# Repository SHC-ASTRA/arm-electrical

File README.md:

# Arm Electrical

Includes the KiCAD files for the Socket and Digit PCBs; Socket is located at the base of Arm and controls the Arm's main joints, Digit is located at the end of Arm and controls Wrist and End Effector.

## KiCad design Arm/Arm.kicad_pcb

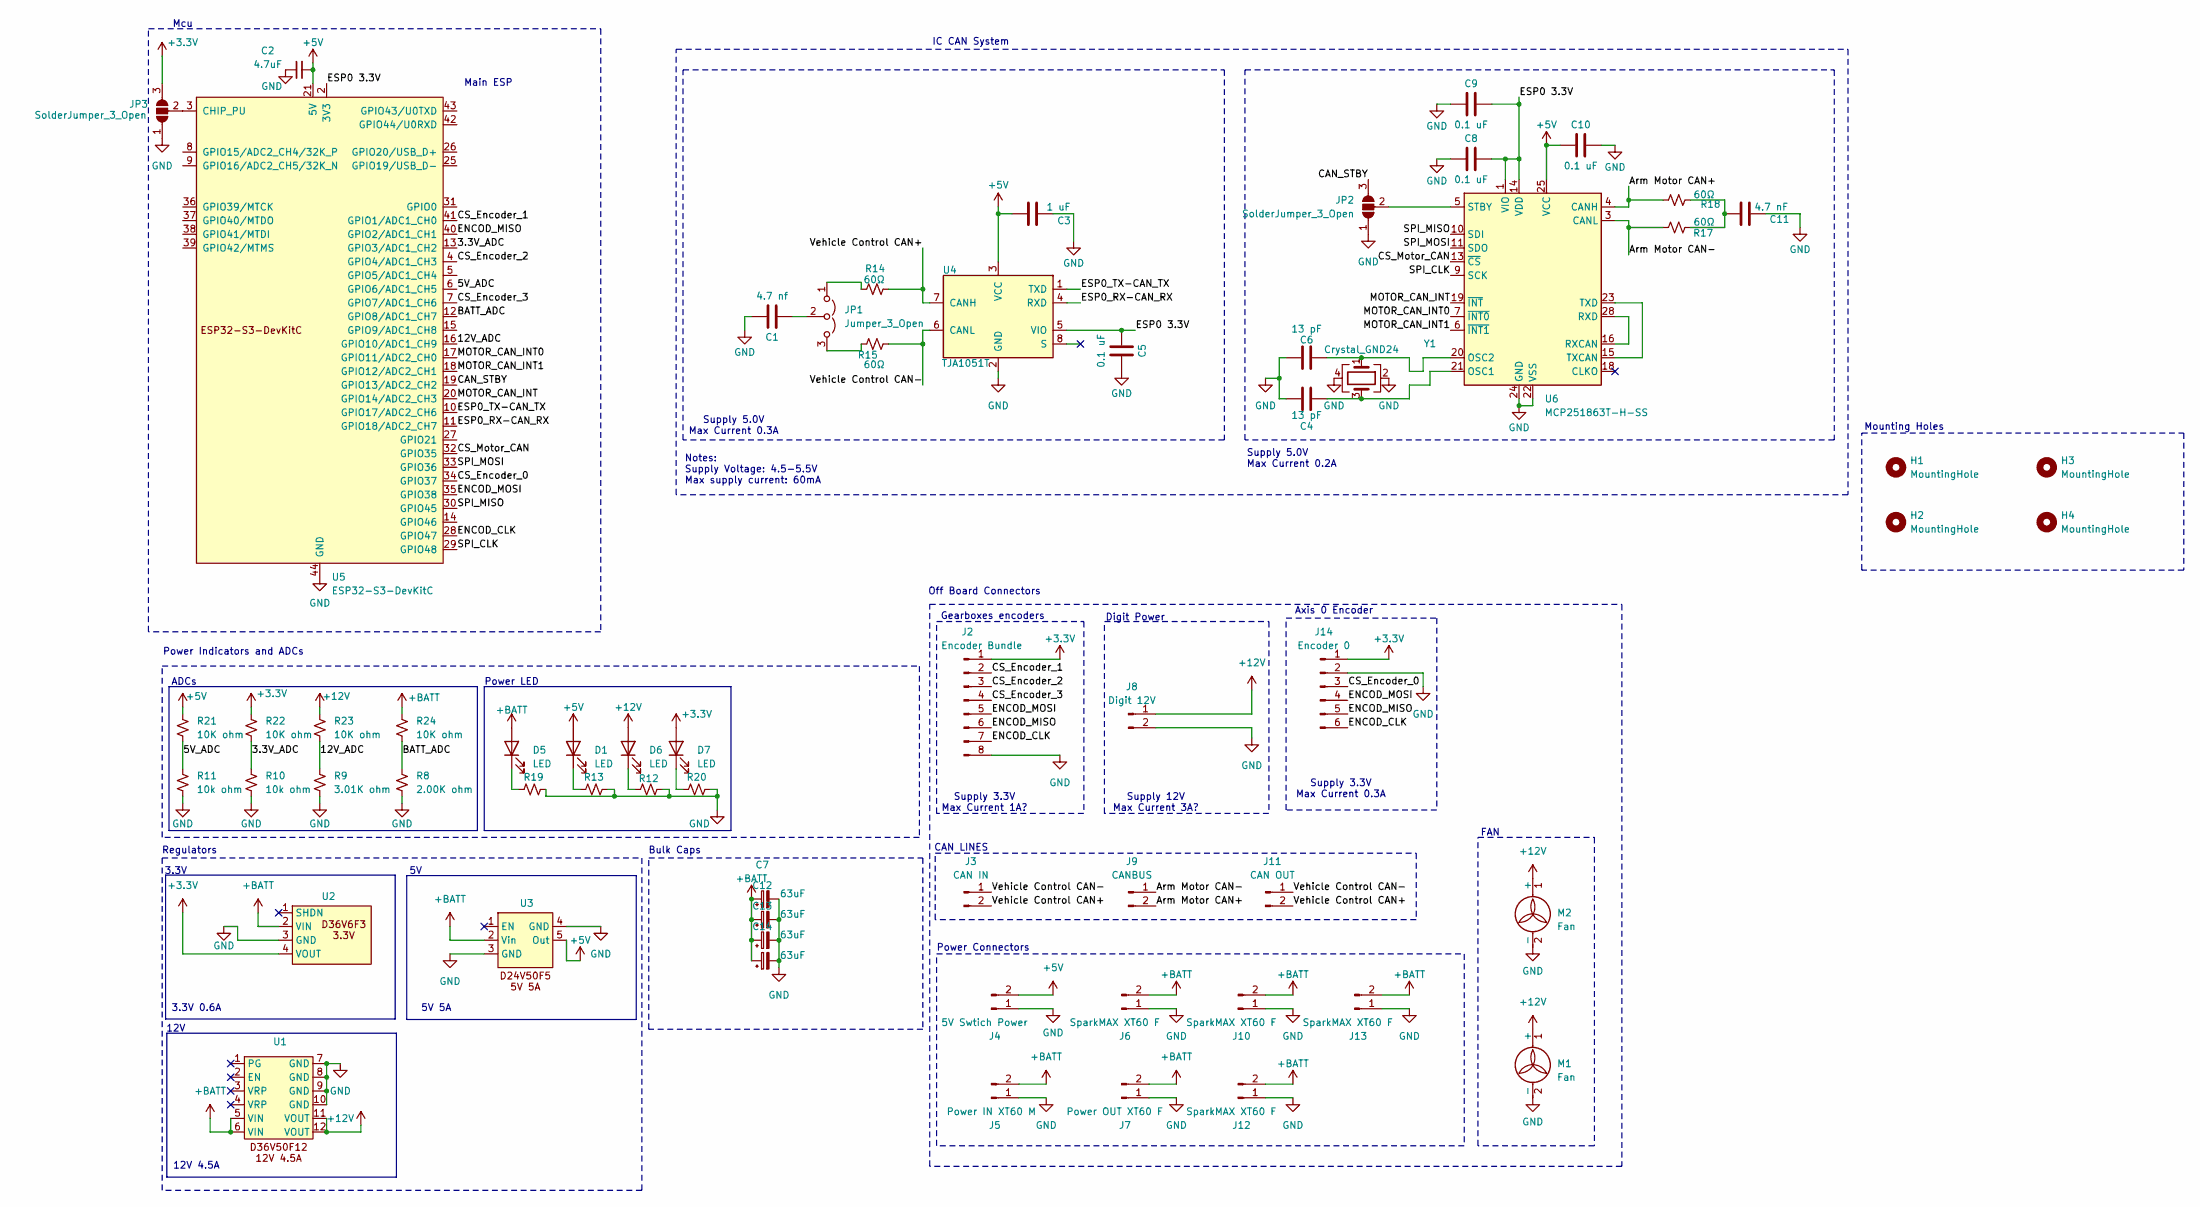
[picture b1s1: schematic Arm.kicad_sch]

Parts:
C1: 4.7 nf; C_0603_1608Metric_Pad1.08x0.95mm_HandSolder
C2: 4.7uF; C_0603_1608Metric_Pad1.08x0.95mm_HandSolder
C3: 1 uF; C_0603_1608Metric_Pad1.08x0.95mm_HandSolder
C4, C6: 13 pF; C_0603_1608Metric_Pad1.08x0.95mm_HandSolder
C5, C8, C9, C10: 0.1 uF; C_0603_1608Metric_Pad1.08x0.95mm_HandSolder
C7, C12, C13, C14: 63uF; CP_Elec_6.3x7.7
C11: 4.7 nF; C_0603_1608Metric_Pad1.08x0.95mm_HandSolder
D1, D5, D6, D7: LED; LED_0603_1608Metric_Pad1.05x0.95mm_HandSolder
H1, H2, H3, H4: MountingHole; MountingHole_3.2mm_M3_DIN965_Pad_TopBottom
J2: Encoder Bundle; Molex_Mini-Fit_Jr_5566-08A_2x04_P4.20mm_Vertical
J3: CAN IN; AMASS_XT30U-F_1x02_P5.0mm_Vertical
J4: 5V Swtich Power; Molex_Mini-Fit_Jr_5566-02A_2x01_P4.20mm_Vertical
J5: Power IN XT60 M; AMASS_XT60-M_1x02_P7.20mm_Vertical
J6, J10, J12, J13: SparkMAX XT60 F; AMASS_XT60-F_1x02_P7.20mm_Vertical
J7: Power OUT XT60 F; AMASS_XT60-F_1x02_P7.20mm_Vertical
J8: Digit 12V; AMASS_XT30U-F_1x02_P5.0mm_Vertical
J9: CANBUS; AMASS_XT30U-F_1x02_P5.0mm_Vertical
J11: CAN OUT; AMASS_XT30U-F_1x02_P5.0mm_Vertical
J14: Encoder 0; Molex_Mini-Fit_Jr_5566-06A_2x03_P4.20mm_Vertical
JP1: Jumper_3_Open; PinHeader_1x03_P2.54mm_Vertical
JP2, JP3: SolderJumper_3_Open; SolderJumper-3_P1.3mm_Open_RoundedPad1.0x1.5mm
M1, M2: Fan; Molex_Mini-Fit_Jr_5566-02A_2x01_P4.20mm_Vertical
R8: 2.00K ohm; R_0603_1608Metric_Pad0.98x0.95mm_HandSolder
R9: 3.01K ohm; R_0603_1608Metric_Pad0.98x0.95mm_HandSolder
R10, R11: 10k ohm; R_0603_1608Metric_Pad0.98x0.95mm_HandSolder
R12, R13, R20: R_Small_US; R_0603_1608Metric_Pad0.98x0.95mm_HandSolder
R14, R15, R17, R18: 60Ω; R_0603_1608Metric_Pad0.98x0.95mm_HandSolder
R19: 2k ohm; R_0603_1608Metric_Pad0.98x0.95mm_HandSolder
R21, R22, R23, R24: 10K ohm; R_0603_1608Metric_Pad0.98x0.95mm_HandSolder
U1: D36V50F12
U2: D36V6F3 3.3V
U3: D24V50F5
U4: TJA1051T; SOIC-8_3.9x4.9mm_P1.27mm
U5: ESP32-S3-DevKitC
U6: MCP251863T-H-SS; SSOP-28_5.3x10.2mm_P0.65mm
Y1: Crystal_GND24; Crystal_SMD_3225-4Pin_3.2x2.5mm_HandSoldering

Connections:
+3.3V: D7.2 (A), J2.1, J14.1, JP3.3 (B), R22.1, U2.4 (VOUT)
+5V: C2.2, C3.1, C10.2, D1.2 (A), J4.2, R21.1, U3.5 (Out), U4.3 (VCC), U5.21 (5V), U6.25 (VCC)
+12V: D6.2 (A), J8.1, M1.1 (+), M2.1 (+), R23.1, U1.11 (VOUT), U1.12 (VOUT)
+BATT: C7.1, C12.1, C13.1, C14.1, D5.2 (A), J5.2, J6.2, J7.2, J10.2, J12.2, J13.2, R24.1, U1.5 (VIN), U1.6 (VIN), U2.2 (VIN), U3.2 (Vin)
/3.3V_ADC: R10.1, R22.2, U5.13 (GPIO3/ADC1_CH2)
/5V_ADC: R11.1, R21.2, U5.6 (GPIO6/ADC1_CH5)
/12V_ADC: R9.1, R23.2, U5.16 (GPIO10/ADC1_CH9)
/Arm Motor CAN+: J9.2, R18.2, U6.4 (CANH)
/Arm Motor CAN-: J9.1, R17.1, U6.3 (CANL)
/BATT_ADC: R8.1, R24.2, U5.12 (GPIO8/ADC1_CH7)
/CAN_STBY: JP2.3 (B), U5.19 (GPIO13/ADC2_CH2)
/CS_Encoder_0: J14.3, U5.34 (GPIO37)
/CS_Encoder_1: J2.2, U5.41 (GPIO1/ADC1_CH0)
/CS_Encoder_2: J2.3, U5.4 (GPIO4/ADC1_CH3)
/CS_Encoder_3: J2.4, U5.7 (GPIO7/ADC1_CH6)
/CS_Motor_CAN: U5.32 (GPIO35), U6.13 (~CS)
/ENCOD_CLK: J2.7, J14.6, U5.28 (GPIO47)
/ENCOD_MISO: J2.6, J14.5, U5.40 (GPIO2/ADC1_CH1)
/ENCOD_MOSI: J2.5, J14.4, U5.35 (GPIO38)
/ESP0 3.3V: C5.2, C8.1, C9.1, U4.5 (VIO), U5.1 (3V3), U5.2 (3V3), U6.1 (VIO), U6.14 (VDD)
/ESP0_RX-CAN_RX: U4.4 (RXD), U5.11 (GPIO18/ADC2_CH7)
/ESP0_TX-CAN_TX: U4.1 (TXD), U5.10 (GPIO17/ADC2_CH6)
/MOTOR_CAN_INT: U5.20 (GPIO14/ADC2_CH3), U6.19 (~INT)
/MOTOR_CAN_INT0: U5.17 (GPIO11/ADC2_CH0), U6.7 (~INT0)
/MOTOR_CAN_INT1: U5.18 (GPIO12/ADC2_CH1), U6.6 (~INT1)
/SPI_CLK: U5.29 (GPIO48), U6.9 (SCK)
/SPI_MISO: U5.30 (GPIO45), U6.10 (SDI)
/SPI_MOSI: U5.33 (GPIO36), U6.11 (SDO)
/Vehicle Control CAN+: J3.2, J11.2, R14.1, U4.7 (CANH)
/Vehicle Control CAN-: J3.1, J11.1, R15.2, U4.6 (CANL)
GND: C1.1, C2.1, C3.2, C4.1, C5.1, C6.1, C7.2, C8.2, C9.2, C10.1, C11.1, C12.2, C13.2, C14.2, J2.8, J4.1, J5.1, J6.1, J7.1, J8.2, J10.1, J12.1, J13.1, J14.2, JP2.1 (A), JP3.1 (A), M1.2 (-), M2.2 (-), R8.2, R9.2, R10.2, R11.2, R12.2, R13.2, R19.2, R20.2, U1.7 (GND), U1.8 (GND), U1.9 (GND), U1.10 (GND), U2.3 (GND), U3.3 (GND), U3.4 (GND), U4.2 (GND), U5.22 (GND), U5.23 (GND), U5.24 (GND), U5.44 (GND), U6.22 (VSS), U6.24 (GND), Y1.2, Y1.4
unnamed: C11.2, R17.2, R18.1
unnamed: D1.1 (K), R13.1
unnamed: D5.1 (K), R19.1
unnamed: D6.1 (K), R12.1
unnamed: D7.1 (K), R20.1
unnamed: JP1.1 (A), R14.2
unnamed: JP1.3 (B), R15.1
unnamed: C1.2, JP1.2 (C)
unnamed: JP2.2 (C), U6.5 (STBY)
unnamed: JP3.2 (C), U5.3 (CHIP_PU)
unnamed: C4.2, U6.21 (OSC1), Y1.3
unnamed: C6.2, U6.20 (OSC2), Y1.1
unnamed: U6.16 (RXCAN), U6.28 (RXD)
unnamed: U6.15 (TXCAN), U6.23 (TXD)

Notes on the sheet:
Supply 5.0V Max Current 0.2A
IC CAN System
CAN LINES
Power LED
Digit Power
3.3V 0.6A
12V
ADCs
Mcu
Notes: Supply Voltage: 4.5-5.5V Max supply current: 60mA
Bulk Caps
Supply 3.3V Max Current 0.3A
Off Board Connectors
Main ESP
Regulators
Axis 0 Encoder
5V 5A
Power Indicators and ADCs
12V 4.5A
Gearboxes encoders
Power Connectors
Mounting Holes
Supply 3.3V Max Current 1A?
Supply 5.0V Max Current 0.3A
Supply 12V Max Current 3A?
FAN
3.3V

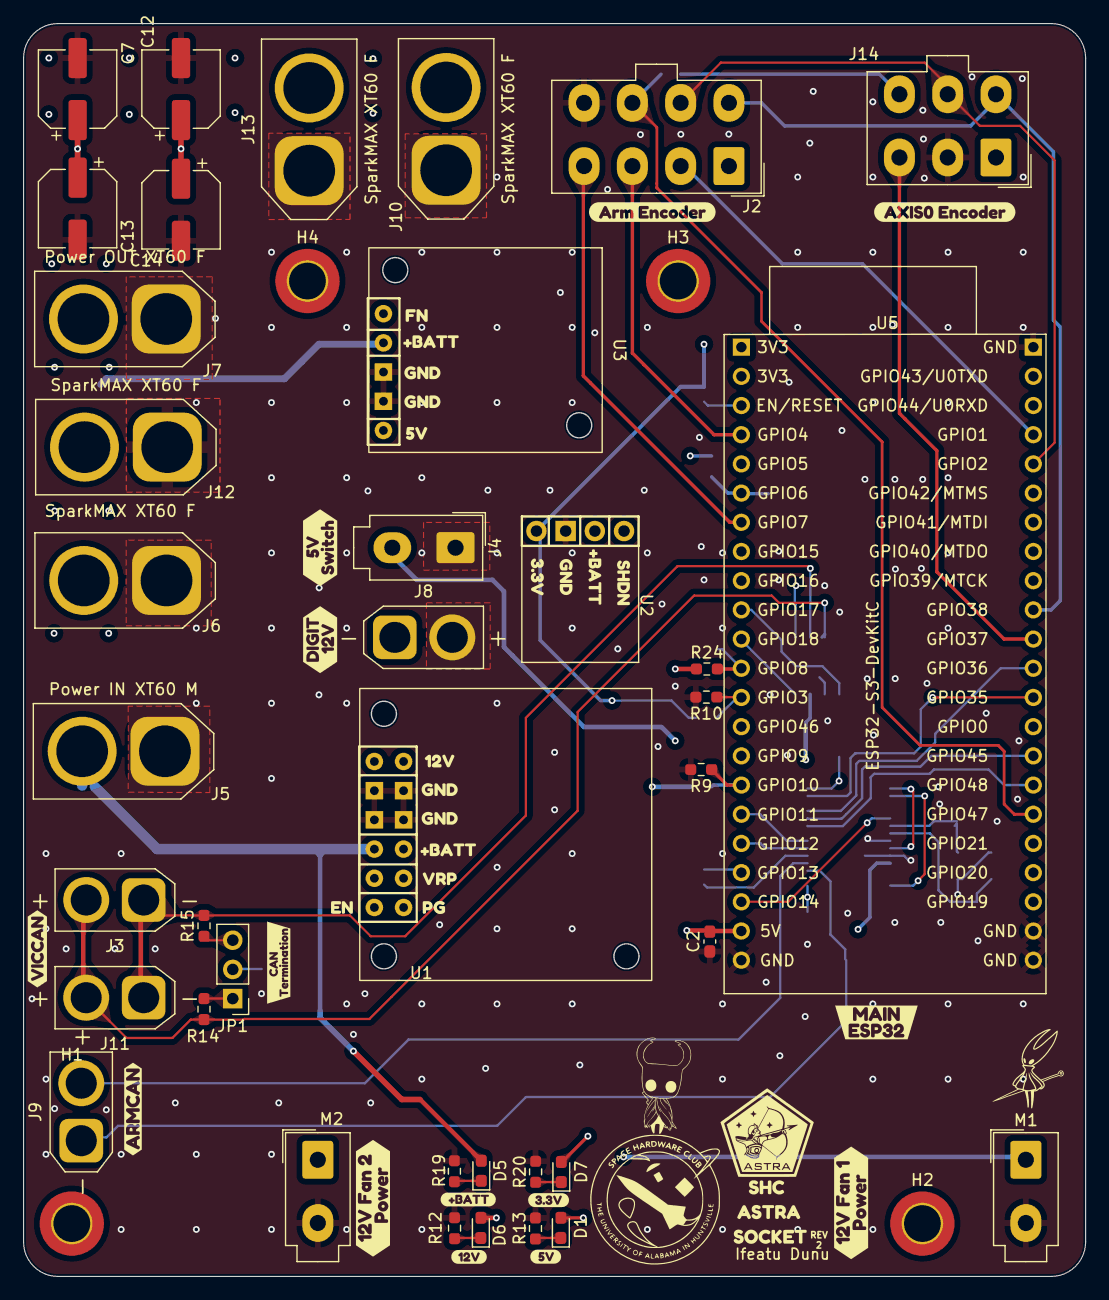
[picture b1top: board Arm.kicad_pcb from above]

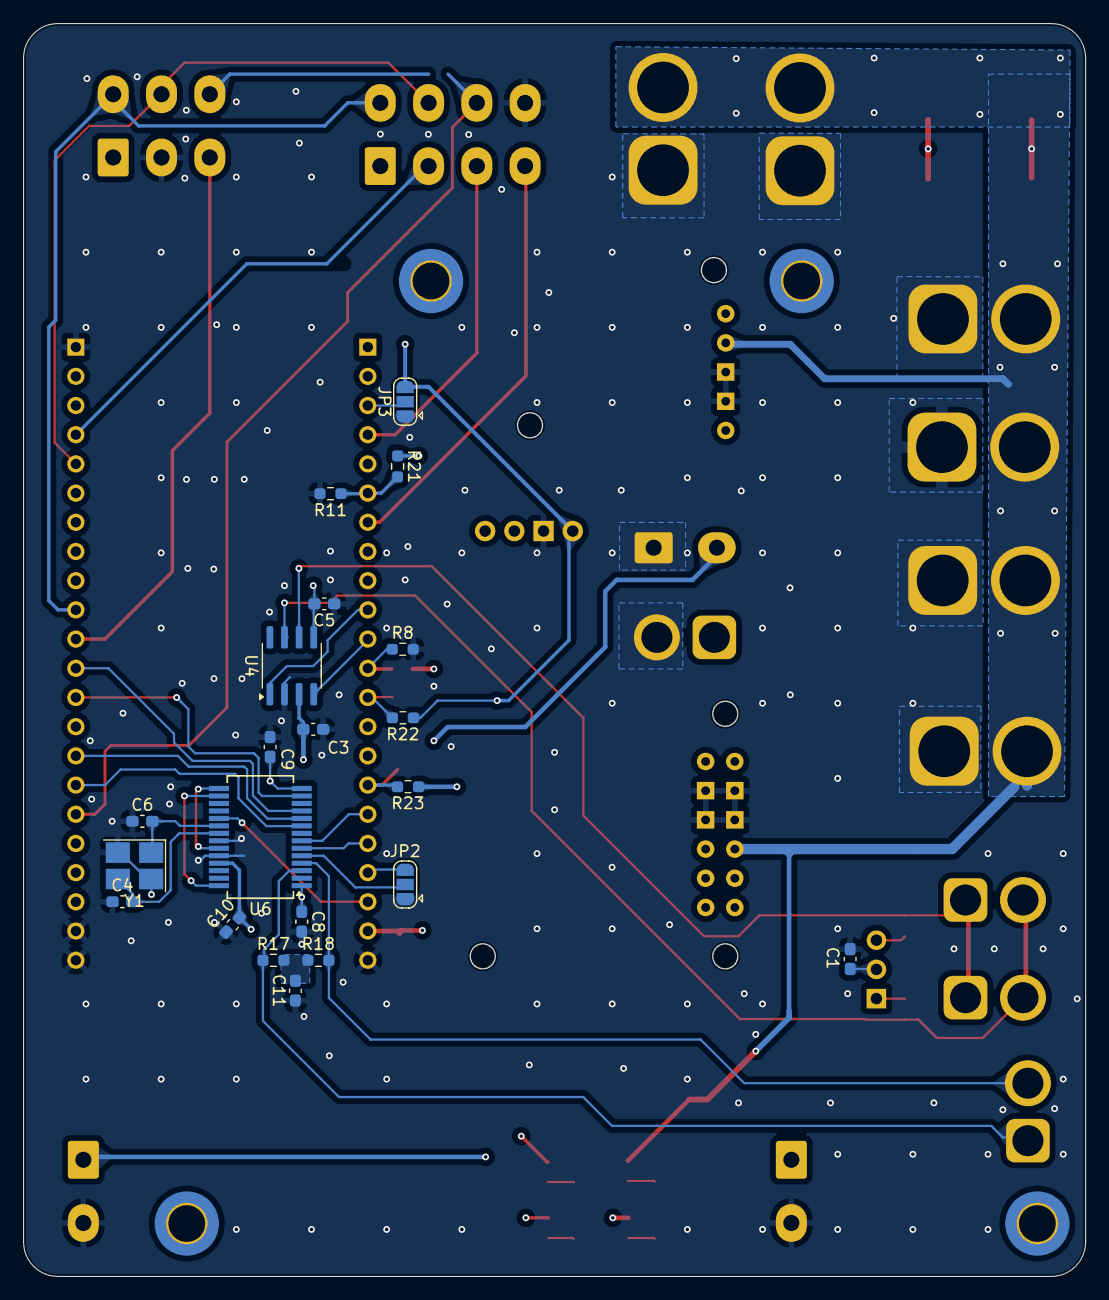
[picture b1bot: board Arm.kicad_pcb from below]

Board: 4 copper layers, 92.4 x 109.0 mm, 94 parts (21 on the bottom side), 45 nets.

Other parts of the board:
kibuzzard-69B0C619: G***; kibuzzard-69B0C619
kibuzzard-69CF1CE3: G***; kibuzzard-69CF1CE3
kibuzzard-69CF1F55: G***; kibuzzard-69CF1F55
kibuzzard-696ED4E2: G***; kibuzzard-696ED4E2
kibuzzard-696ED4F2: G***; kibuzzard-696ED4F2
kibuzzard-696ED4F9: G***; kibuzzard-696ED4F9
kibuzzard-696ED8B0: G***; kibuzzard-696ED8B0
kibuzzard-696EDF62: G***; kibuzzard-696EDF62
kibuzzard-696EDF69: G***; kibuzzard-696EDF69
kibuzzard-696EDF70: G***; kibuzzard-696EDF70
kibuzzard-696EDFA6: G***; kibuzzard-696EDFA6
kibuzzard-696EDFDB: G***; kibuzzard-696EDFDB
kibuzzard-696EDFE7: G***; kibuzzard-696EDFE7
kibuzzard-696EDFF0: G***; kibuzzard-696EDFF0
kibuzzard-696EE00B: G***; kibuzzard-696EE00B
kibuzzard-696EEF9E: G***; kibuzzard-696EEF9E
kibuzzard-696EEFE3: G***; kibuzzard-696EEFE3
kibuzzard-696EF04A: G***; kibuzzard-696EF04A
kibuzzard-696EF05A: G***; kibuzzard-696EF05A
kibuzzard-699F8EAF: G***; kibuzzard-699F8EAF
kibuzzard-69541FE4: G***; kibuzzard-69541FE4
kibuzzard-69701E52: G***; kibuzzard-69701E52
kibuzzard-69783B26: G***; kibuzzard-69783B26
kibuzzard-697025BA: G***; kibuzzard-697025BA
kibuzzard-6954203E: G***; kibuzzard-6954203E
kibuzzard-6970222E: G***; kibuzzard-6970222E
kibuzzard-6970240E: G***; kibuzzard-6970240E
kibuzzard-69542020, kibuzzard-69542020#2: G***; kibuzzard-69542020
kibuzzard-69702208: G***; kibuzzard-69702208
kibuzzard-69702591: G***; kibuzzard-69702591

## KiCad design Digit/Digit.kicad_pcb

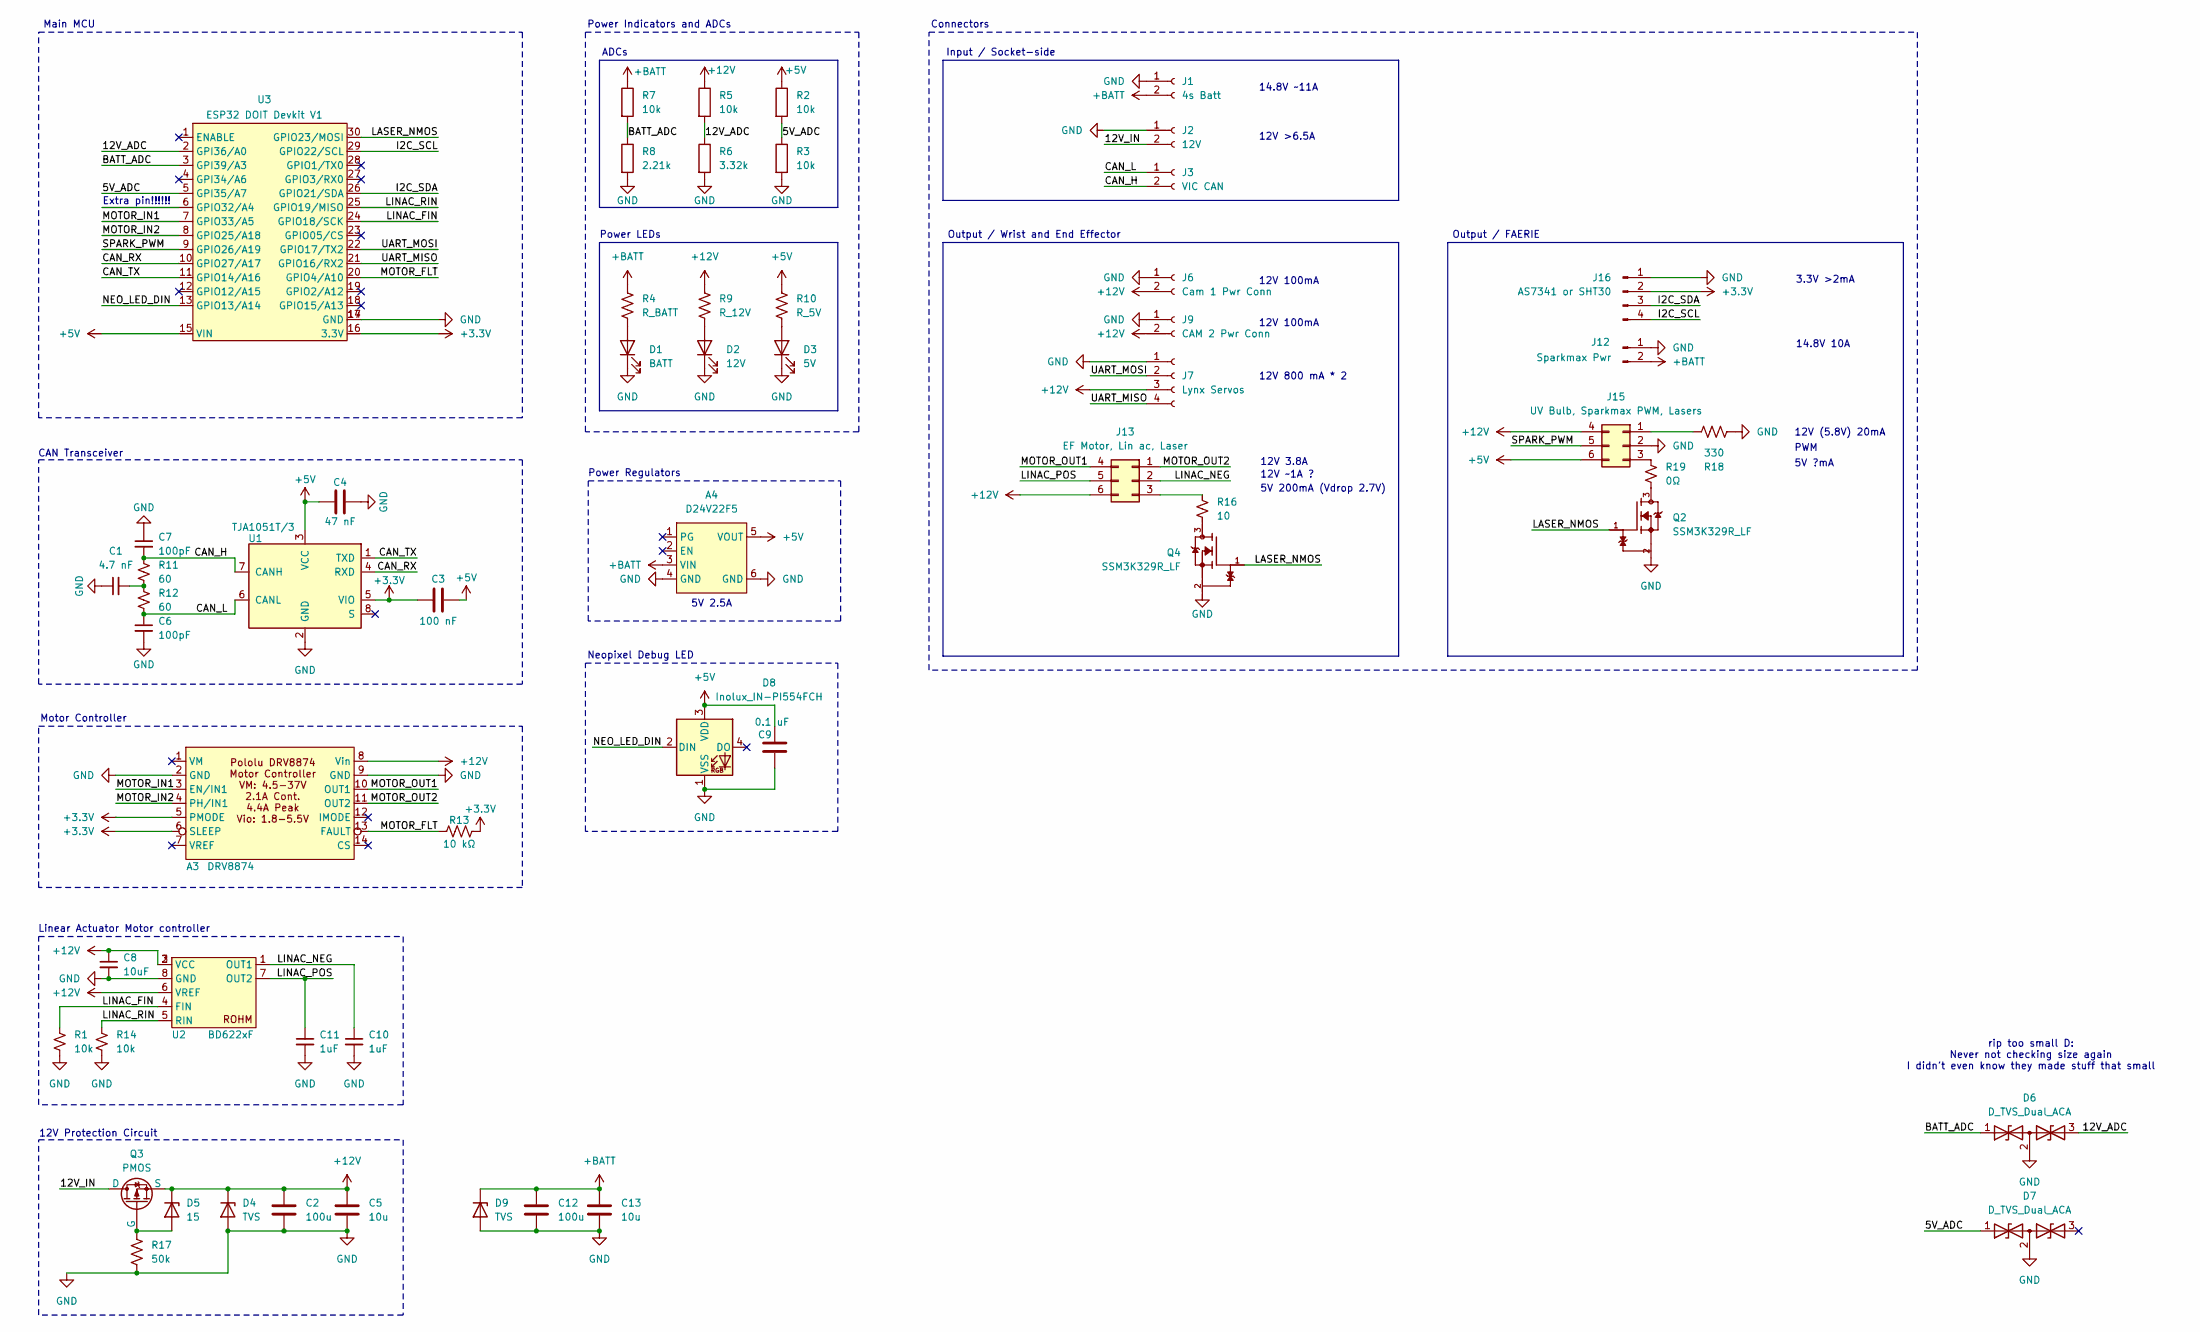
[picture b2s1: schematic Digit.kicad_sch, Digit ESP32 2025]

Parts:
A3: DRV8874
A4: D24V22F5; D24V22Fx
C1: 4.7 nF; C_0603_1608Metric_Pad1.08x0.95mm_HandSolder
C2, C12: 100u; C_0603_1608Metric_Pad1.08x0.95mm_HandSolder
C3: 100 nF; C_0603_1608Metric_Pad1.08x0.95mm_HandSolder
C4: 47 nF; C_0603_1608Metric_Pad1.08x0.95mm_HandSolder
C5, C13: 10u; C_0603_1608Metric_Pad1.08x0.95mm_HandSolder
C6, C7: 100pF; C_0603_1608Metric_Pad1.08x0.95mm_HandSolder
C8: 10uF; C_0603_1608Metric_Pad1.08x0.95mm_HandSolder
C9: 0.1 uF; C_0603_1608Metric_Pad1.08x0.95mm_HandSolder
C10, C11: 1uF; C_0603_1608Metric_Pad1.08x0.95mm_HandSolder
D1: BATT; LED_0603_1608Metric_Pad1.05x0.95mm_HandSolder
D2: 12V; LED_0603_1608Metric_Pad1.05x0.95mm_HandSolder
D3: 5V; LED_0603_1608Metric_Pad1.05x0.95mm_HandSolder
D4, D9: TVS; SOD-323HEUS2H_TOS
D5: 15; D_SOD-123
D6, D7: D_TVS_Dual_ACA; SG-WLL-3-1
D8: Inolux_IN-PI554FCH; LED_Inolux_IN-PI554FCH_PLCC4_5.0x5.0mm_P3.2mm
J1: 4s Batt; AMASS_XT60PW-M_1x02_P7.20mm_Horizontal
J2: 12V; AMASS_XT30PW-M_1x02_P2.50mm_Horizontal
J3: VIC CAN; AMASS_XT30PW-F_1x02_P2.50mm_Horizontal
J6: Cam 1 Pwr Conn; AMASS_XT30U-F_1x02_P5.0mm_Vertical
J7: Lynx Servos; Molex_Mini-Fit_Jr_5566-04A_2x02_P4.20mm_Vertical
J9: CAM 2 Pwr Conn; AMASS_XT30U-F_1x02_P5.0mm_Vertical
J12: Sparkmax Pwr; AMASS_XT60PW-F_1x02_P7.20mm_Horizontal
J13: EF Motor, Lin ac, Laser; Molex_Mini-Fit_Jr_5566-06A_2x03_P4.20mm_Vertical
J15: UV Bulb, Sparkmax PWM, Lasers; Molex_Mini-Fit_Jr_5566-06A_2x03_P4.20mm_Vertical
J16: AS7341 or SHT30; Molex_Mini-Fit_Jr_5566-04A_2x02_P4.20mm_Vertical
Q2, Q4: SSM3K329R_LF; SOT-23F_TOS; PARTREV 1.0
Q3: PMOS; TO-252-2
R1, R2, R3, R5, R7, R14: 10k; R_0603_1608Metric_Pad0.98x0.95mm_HandSolder
R4: R_BATT; R_0603_1608Metric_Pad0.98x0.95mm_HandSolder
R6: 3.32k; R_0603_1608Metric_Pad0.98x0.95mm_HandSolder
R8: 2.21k; R_0603_1608Metric_Pad0.98x0.95mm_HandSolder
R9: R_12V; R_0603_1608Metric_Pad0.98x0.95mm_HandSolder
R10: R_5V; R_0603_1608Metric_Pad0.98x0.95mm_HandSolder
R11, R12: 60; R_0603_1608Metric_Pad0.98x0.95mm_HandSolder
R13: 10 kΩ; R_0603_1608Metric_Pad0.98x0.95mm_HandSolder
R16: 10; R_0603_1608Metric_Pad0.98x0.95mm_HandSolder
R17: 50k; R_0603_1608Metric_Pad0.98x0.95mm_HandSolder
R18: 330; R_0603_1608Metric_Pad0.98x0.95mm_HandSolder
R19: 0Ω; R_0603_1608Metric_Pad0.98x0.95mm_HandSolder
U1: TJA1051T/3; SOIC-8_3.9x4.9mm_P1.27mm
U2: BD622xF; SOP8_ROM
U3: ESP32 DOIT Devkit V1; esp32_devkit_v1_doit

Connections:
+3.3V: A3.5 (PMODE), A3.6 (SLEEP), C3.2, J16.2, R13.1, U1.5 (VIO), U3.16 (3.3V)
+5V: A4.5 (VOUT), C3.1, C4.1, C9.1, D8.3 (VDD), J15.6, R2.1, R10.1, U1.3 (VCC), U3.15 (VIN)
+12V: A3.8 (Vin), C2.1, C5.1, C8.1, D4.1 (K), D5.1 (K), J6.2, J7.3, J9.2, J13.6, J15.4, Q3.3 (S), R5.1, R9.1, U2.2 (VCC), U2.3 (VCC), U2.6 (VREF)
+BATT: A4.3 (VIN), C12.1, C13.1, D9.1 (K), J1.2, J12.2, R4.1, R7.1
/5V_ADC: D7.1 (A1), R2.2, R3.1, U3.5 (GPI35/A7)
/12V_ADC: D6.3 (A2), R5.2, R6.1, U3.2 (GPI36/A0)
/12V_IN: J2.2, Q3.1 (D)
/BATT_ADC: D6.1 (A1), R7.2, R8.1, U3.3 (GPI39/A3)
/CAN_H: C7.2, J3.2, R11.1, U1.7 (CANH)
/CAN_L: C6.1, J3.1, R12.2, U1.6 (CANL)
/CAN_RX: U1.4 (RXD), U3.10 (GPIO27/A17)
/CAN_TX: U1.1 (TXD), U3.11 (GPIO14/A16)
/I2C_SCL: J16.4, U3.29 (GPIO22/SCL)
/I2C_SDA: J16.3, U3.26 (GPIO21/SDA)
/LASER_NMOS: Q2.1, Q4.1, U3.30 (GPIO23/MOSI)
/LINAC_FIN: R1.2, U2.4 (FIN), U3.24 (GPIO18/SCK)
/LINAC_NEG: C10.1, J13.2, U2.1 (OUT1)
/LINAC_POS: C11.1, J13.5, U2.7 (OUT2)
/LINAC_RIN: R14.2, U2.5 (RIN), U3.25 (GPIO19/MISO)
/MOTOR_FLT: A3.13 (FAULT), R13.2, U3.20 (GPIO4/A10)
/MOTOR_IN1: A3.3 (EN/IN1), U3.7 (GPIO33/A5)
/MOTOR_IN2: A3.4 (PH/IN1), U3.8 (GPIO25/A18)
/MOTOR_OUT1: A3.10 (OUT1), J13.4
/MOTOR_OUT2: A3.11 (OUT2), J13.1
/NEO_LED_DIN: D8.2 (DIN), U3.13 (GPIO13/A14)
/SPARK_PWM: J15.5, U3.9 (GPIO26/A19)
/UART_MISO: J7.4, U3.21 (GPIO16/RX2)
/UART_MOSI: J7.2, U3.22 (GPIO17/TX2)
GND: A3.2 (GND), A3.9 (GND), A4.4 (GND), A4.6 (GND), C1.1, C2.2, C4.2, C5.2, C6.2, C7.1, C8.2, C9.2, C10.2, C11.2, C12.2, C13.2, D1.1 (K), D2.1 (K), D3.1 (K), D4.2 (A), D6.2 (common), D7.2 (common), D8.1 (VSS), D9.2 (A), J1.1, J2.1, J6.1, J7.1, J9.1, J12.1, J15.2, J16.1, Q2.2, Q4.2, R1.1, R3.2, R6.2, R8.2, R14.1, R17.2, R18.2, U1.2 (GND), U2.8 (GND), U3.14 (GND), U3.17 (GND)
unnamed: C1.2, R11.2, R12.1
unnamed: D1.2 (A), R4.2
unnamed: D2.2 (A), R9.2
unnamed: D3.2 (A), R10.2
unnamed: D5.2 (A), Q3.2 (G), R17.1
unnamed: J13.3, R16.1
unnamed: J15.1, R18.1
unnamed: J15.3, R19.1
unnamed: Q2.3, R19.2
unnamed: Q4.3, R16.2

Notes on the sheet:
12V (5.8V) 20mA
Input / Socket-side
Power Regulators
PWM
ADCs
12V Protection Circuit
5V 2.5A
3.3V >2mA
14.8V ~11A
Linear Actuator Motor controller
12V 100mA
Motor Controller
CAN Transceiver
12V >6.5A
rip too small D: Never not checking size again I didn't even know they made stuff that small
Power LEDs
5V 200mA (Vdrop 2.7V)
12V ~1A ?
Output / Wrist and End Effector
5V ?mA
Main MCU
12V 3.8A
12V 800 mA * 2
Neopixel Debug LED
14.8V 10A
Power Indicators and ADCs
Extra pin!!!!!!
Output / FAERIE
Connectors

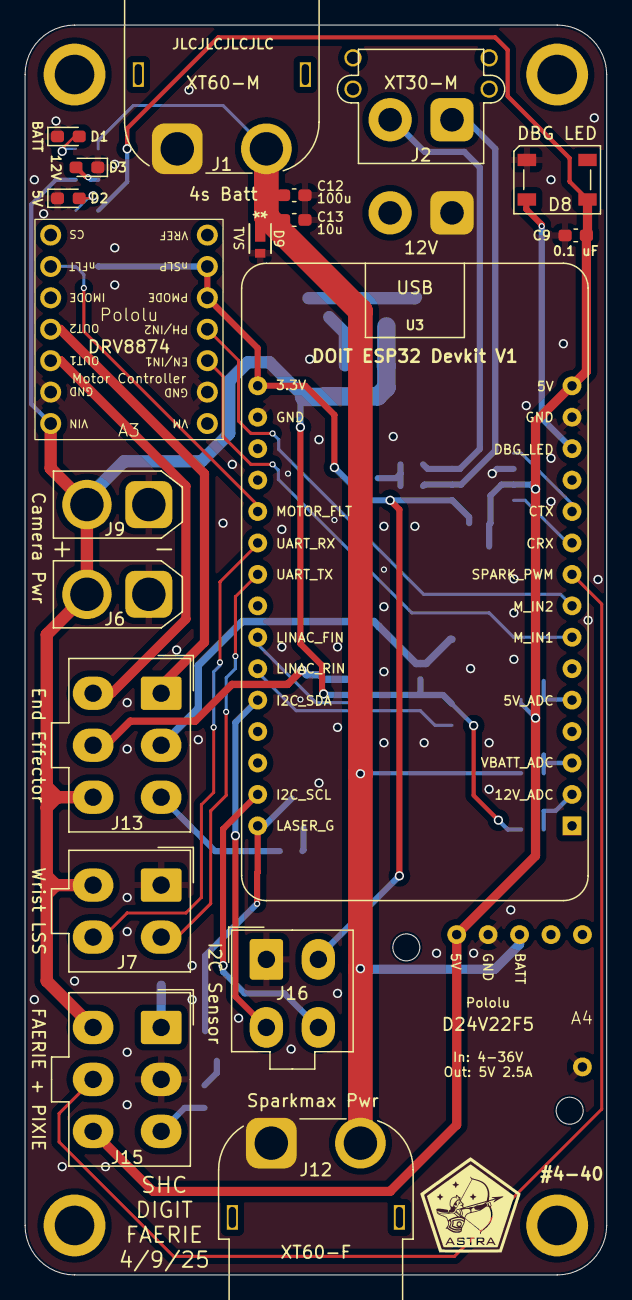
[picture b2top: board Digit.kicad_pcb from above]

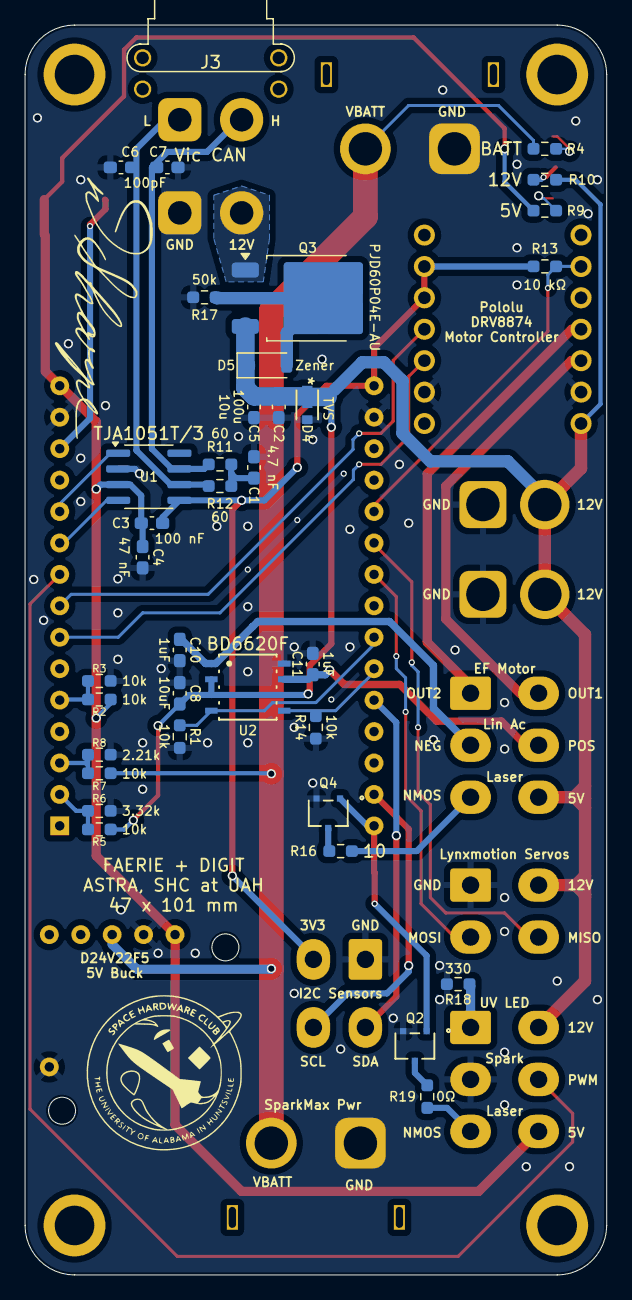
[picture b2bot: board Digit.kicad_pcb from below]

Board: 2 copper layers, 47.0 x 101.0 mm, 60 parts (36 on the bottom side), 39 nets.

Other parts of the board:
H1, H2, H3, H4: MountingHole_3.2mm_M3

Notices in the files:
README.md:
License: AGPL v3
